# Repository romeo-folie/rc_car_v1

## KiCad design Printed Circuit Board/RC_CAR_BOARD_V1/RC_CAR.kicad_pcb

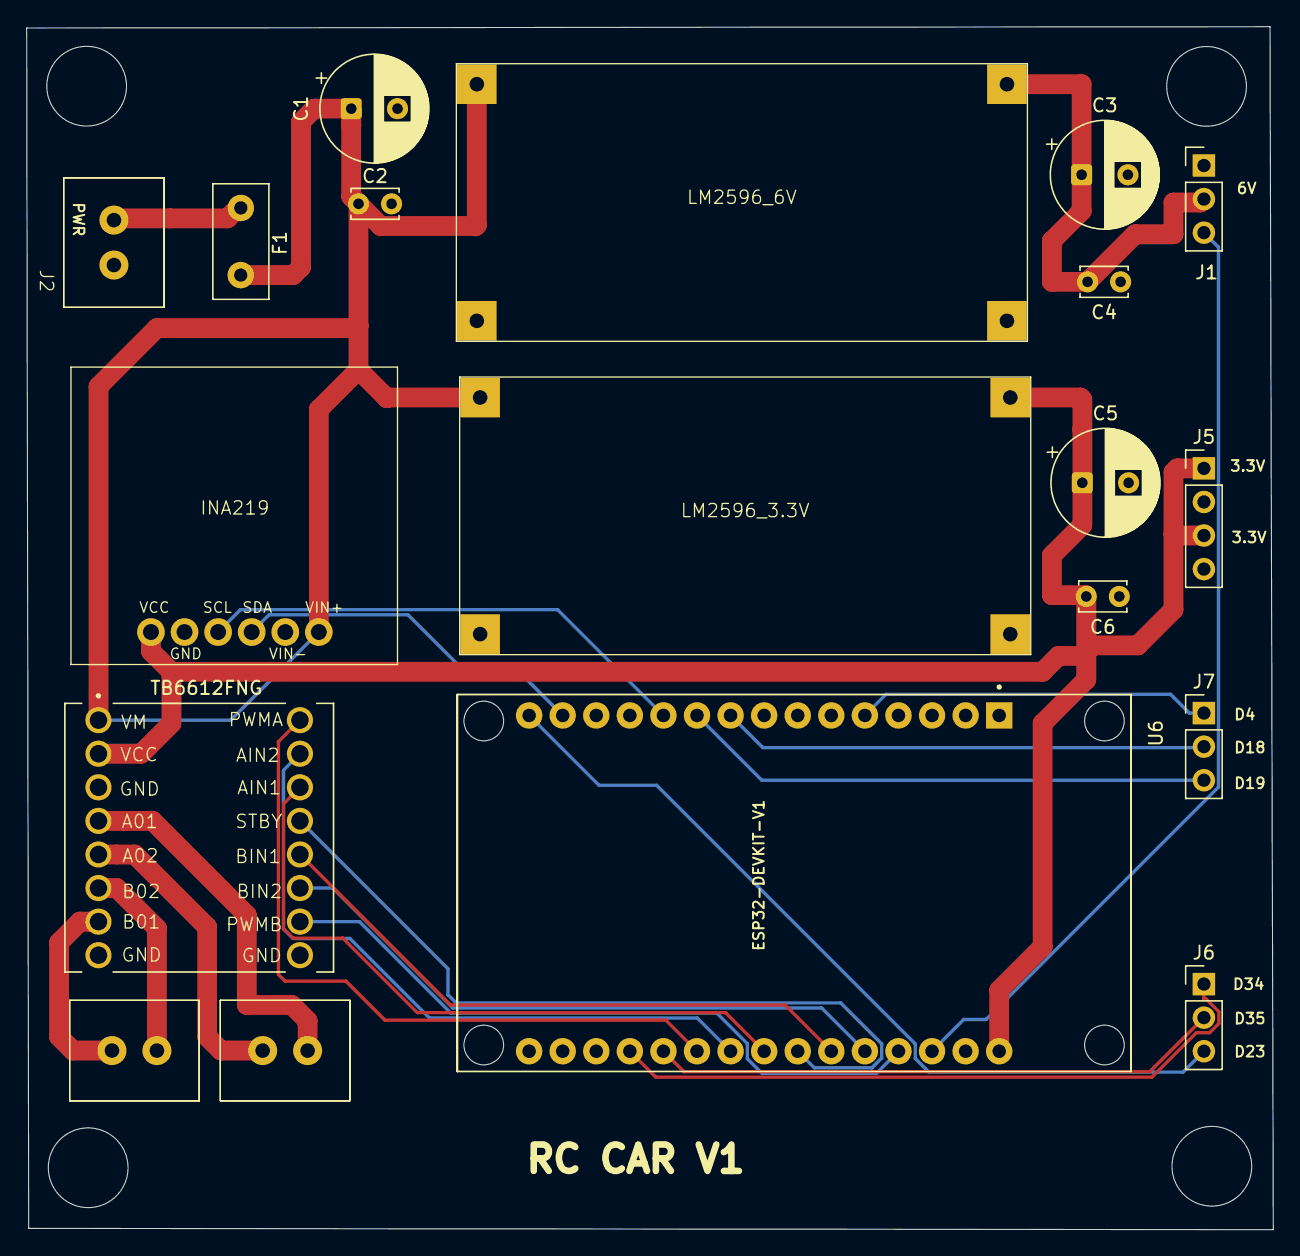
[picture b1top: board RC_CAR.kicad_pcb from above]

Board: 4 copper layers, 94.3 x 91.0 mm, 19 parts (0 on the bottom side), 25 nets.

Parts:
C1, C3, C5: C_Polarized; CP_Radial_D8.0mm_P3.50mm
C2, C4, C6: C; C_Disc_D3.4mm_W2.1mm_P2.50mm
F1: Polyfuse; Fuse_Littelfuse_395Series
INA219: INA219_Module
J1, J6, J7: Conn_01x03_Pin; PinHeader_1x03_P2.54mm_Vertical
J2, J3, J4: Screw_Terminal_01x02; ScrewTerminal_01x02_Custom_4.5mm
J5: Conn_01x04_Pin; PinHeader_1x04_P2.54mm_Vertical
LM2596_3.3V, LM2596_6V: LM2596S_Module
U3: ROB-14450; MODULE_ROB-14450
U6: ESP32-DEVKIT-V1; MODULE_ESP32_DEVKIT_V1

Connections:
+3.3V: C5.1, C6.2, INA219.1 (VCC), J5.1, J5.3, LM2596_3.3V.3 (OUT+), U3.2 (VCC), U6.30 (VIN)
+6V: C3.1, C4.2, J1.2, LM2596_6V.3 (OUT+)
+7.5V: C1.1, C2.1, F1.2, INA219.6 (VIN+), LM2596_3.3V.1 (IN+), LM2596_6V.1 (IN+), U3.1 (VM)
GND: C1.2, C2.2, C3.2, C4.1, C5.2, C6.1, INA219.2 (GND), INA219.5 (VIN-), J1.1, J2.1, J5.2, J5.4, LM2596_3.3V.2 (IN-), LM2596_3.3V.4 (OUT-), LM2596_6V.2 (IN-), LM2596_6V.4 (OUT-), U3.3 (GND), U3.8 (GND), U3.9 (GND), U6.2 (GND), U6.29 (GND)
unnamed: INA219.4 (SCL), U6.14 (D22)
unnamed: INA219.3 (SDA), U6.11 (D21)
unnamed: J1.3, U6.28 (D13)
unnamed: F1.1, J2.2
unnamed: J3.1, U3.4 (A01)
unnamed: J3.2, U3.5 (A02)
unnamed: J4.1, U3.7 (B01)
unnamed: J4.2, U3.6 (B02)
unnamed: J6.1, U6.19 (D34)
unnamed: J6.2, U6.20 (D35)
unnamed: J6.3, U6.15 (D23)
unnamed: J7.1, U6.5 (D4)
unnamed: J7.2, U6.9 (D18)
unnamed: J7.3, U6.10 (D19)
unnamed: U3.14 (AI1), U6.23 (D25)
unnamed: U3.15 (AI2), U6.22 (D33)
unnamed: U3.12 (BI1), U6.25 (D27)
unnamed: U3.11 (BI2), U6.26 (D14)
unnamed: U3.16 (PWMA), U6.21 (D32)
unnamed: U3.10 (PWMB), U6.27 (D12)
unnamed: U3.13 (STBY), U6.24 (D26)

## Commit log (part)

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2025-09-21 added images, pcb files, and 3d models
2025-09-23 removed unnecessary files, simplified dir structure
2025-09-24 add arduino sketch
